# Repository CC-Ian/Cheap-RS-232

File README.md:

# A $1 USB RS-232 Adaptor

RS-232 serial. It's super common when interfacing with test and measure equipment and with microcontrollers. Sometimes, you want a lot of them though, so instead of buying them online, you're best off making them yourself. Plus, these are a little nicer than what you can find online, and a little worse.

It's smaller, lighter, and USB type C, but it lacks some features like RTS, DIR, or CTS pins. It just has the bare necessitites. RX, TX, GND, ad VCC. Plus, it looks slick.

I'd wanted to sell these, but it doesn't make sense. Make them yourself, or integrate this circuit into your own projects.

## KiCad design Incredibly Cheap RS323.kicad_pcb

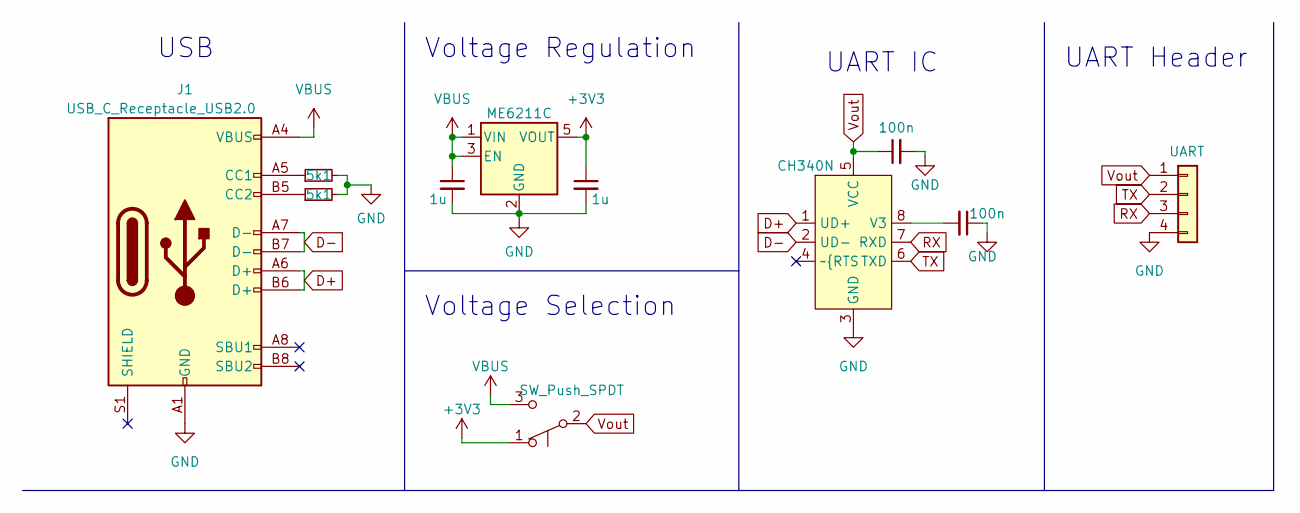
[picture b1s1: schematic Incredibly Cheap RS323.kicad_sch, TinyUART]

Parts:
C1, C2: 100n; C_0402_1005Metric
C3, C4: 1u; C_0402_1005Metric
J1: USB_C_Receptacle_USB2.0; USB_C_Receptacle_HRO_TYPE-C-31-M-12
J3: UART; PinHeader_1x04_P2.54mm_Vertical
R1, R2: 5k1; R_0603_1608Metric
SW1: SW_Push_SPDT; SW_SPDT_PCM12
U1: CH340N; SOP-8_3.9x4.9mm_P1.27mm
U2: ME6211C; SOT-353_SC-70-5

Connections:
+3V3: C4.1, SW1.1 (A), U2.5 (VOUT)
D+: J1.A6 (D+), J1.B6 (D+), U1.1 (UD+)
D-: J1.A7 (D-), J1.B7 (D-), U1.2 (UD-)
GND: C1.2, C2.1, C3.2, C4.2, J1.A1 (GND), J1.A12 (GND), J1.B1 (GND), J1.B12 (GND), J3.4, R1.2, R2.2, U1.3 (GND), U2.2 (GND)
unnamed: C2.2, U1.8 (V3)
unnamed: J1.A5 (CC1), R1.1
unnamed: J1.B5 (CC2), R2.1
RX: J3.3, U1.7 (RXD)
TX: J3.2, U1.6 (TXD)
VBUS: C3.1, J1.A4 (VBUS), J1.A9 (VBUS), J1.B4 (VBUS), J1.B9 (VBUS), SW1.3 (C), U2.1 (VIN), U2.3 (EN)
Vout: C1.1, J3.1, SW1.2 (B), U1.5 (VCC)

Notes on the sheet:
UART IC
Voltage Selection
UART Header
Voltage Regulation
USB

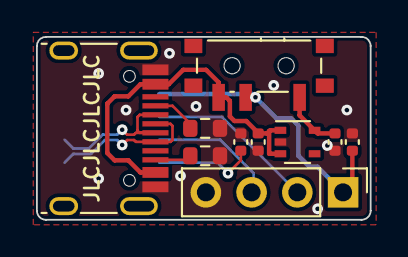
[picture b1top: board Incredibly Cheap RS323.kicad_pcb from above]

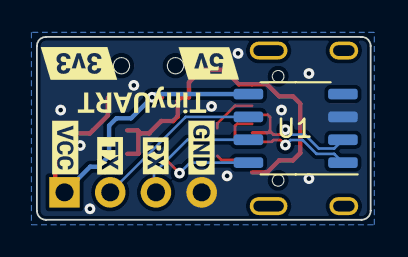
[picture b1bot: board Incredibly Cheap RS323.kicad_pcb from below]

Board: 2 copper layers, 18.5 x 10.2 mm, 18 parts (8 on the bottom side), 11 nets.

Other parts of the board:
kibuzzard-63CD506C: G***; kibuzzard-63CD506C
kibuzzard-63CD525C: G***; kibuzzard-63CD525C
kibuzzard-63CD526B: G***; kibuzzard-63CD526B
kibuzzard-63CD529F: G***; kibuzzard-63CD529F
kibuzzard-63CD5015: G***; kibuzzard-63CD5015
kibuzzard-63CD5248: G***; kibuzzard-63CD5248
kibuzzard-63CD5252: G***; kibuzzard-63CD5252

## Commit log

2023-02-15 Added PCB Files
